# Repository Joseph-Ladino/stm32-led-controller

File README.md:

# STM32 WS2815 LED Controller

This is a hobby project using an STM32 microcontroller to control WS2815 LED strips over ethernet. While it’s a ~fun~ interesting setup, it’s still a work in progress, so the design and code have plenty of room for improvement.

## Hardware Overview

The controller is built around a custom PCB and features:

- **Microcontroller**: STM32G0B0RE, which handles LED effects, strip control, and MQTT connection.
- **Ethernet**: W5500 chip (from Wiznet) for simple 100/10 ethernet functionality.
- **LED Connection**: 4-pin connector for attaching WS2815 LED strips.
- **Debugging Options**:
  - **SWD (Serial Wire Debug)**: Required for flashing firmware.
  - **USB-C Port**: Used mainly for serial output, with optional 5V power.
- **Power Setup**:
  - **12V Power Connector**: Powers the LED strip, switched on/off with a software-controlled load switch. The power connector is subject to change in a future board REV but for now the power leads are attached using M4 machine screws.
  - **Buck Converter**: Steps down 12V to 5V for the data signals to the LEDs and to power the STM32 and ethernet chip.

*Known Issues*: 
  - The pads' hole size for the 4-pin LED strip connector is too small to easily fit the wires.

## Firmware Details

The firmware is written in C++ with portability and extensibility as guiding principles:

- **Connectivity**: Includes partially complete, platform-independent abstractions for network interface, sockets, and MQTT client, allowing connection to MQTT servers. Implementations relies on open-source libraries but the design allows these libraries to be swapped out relatively easily.
- **LED Strip Compatibility**: The firmware’s design allows control beyond the WS2815, with flexibility for WS2812, WS2811, and potentially other types through a semi-extensible interface. Currently, communication is handled by DMA timers and a circular buffer, but this setup supports future implementations.
- **Configurable, Extensible Architecture**: Aiming for maximum configurability, the design focuses on semi-modular components that can be swapped or extended easily.
- **Documentation**: Classes are documented using Doxygen. You can find a compiled HTML version in the `Firmware/Docs` folder.

*Known Issues*: 
  - The MQTT connection intermittently drops despite active ethernet indicators (likely a bug in the reconnect code).

---

## Getting Started

To try it out:

1. **Connect Power and LEDs**:
   - Screw down a 12V power source onto the marked.
   - Attach a WS2815 LED strip to the 4-pin connector.
   
2. **Upload Firmware**:
   - Firmware currently needs to be flashed over the SWD connector.

3. **Run and Debug**:
   - Connect the USB-C port for serial output or use SWD for debugging.

## Specs

| Feature                   | Description                                       |
|---------------------------|---------------------------------------------------|
| Microcontroller           | STM32G0B0RE                                       |
| Ethernet                  | W5500 (100/10 Ethernet)                           |
| LED Output Connector      | 4-pin (for WS2815 LED strip)                      |
| Debugging                 | USB-C, SWD for flashing      |
| Power Input               | 12V screw terminal                                |
| Voltage Conversion        | Buck converter (12V to 5V)                        |
| Data Buffer               | SN74125N for 5V data signals                      |
| Regulator                 | 3.3V for STM32 and W5500                          |

---

### Notes

This project is more of a learning exercise in PCB design and STM32 programming, so it might not be the most optimized controller out there! Any feedback or suggestions are welcome.

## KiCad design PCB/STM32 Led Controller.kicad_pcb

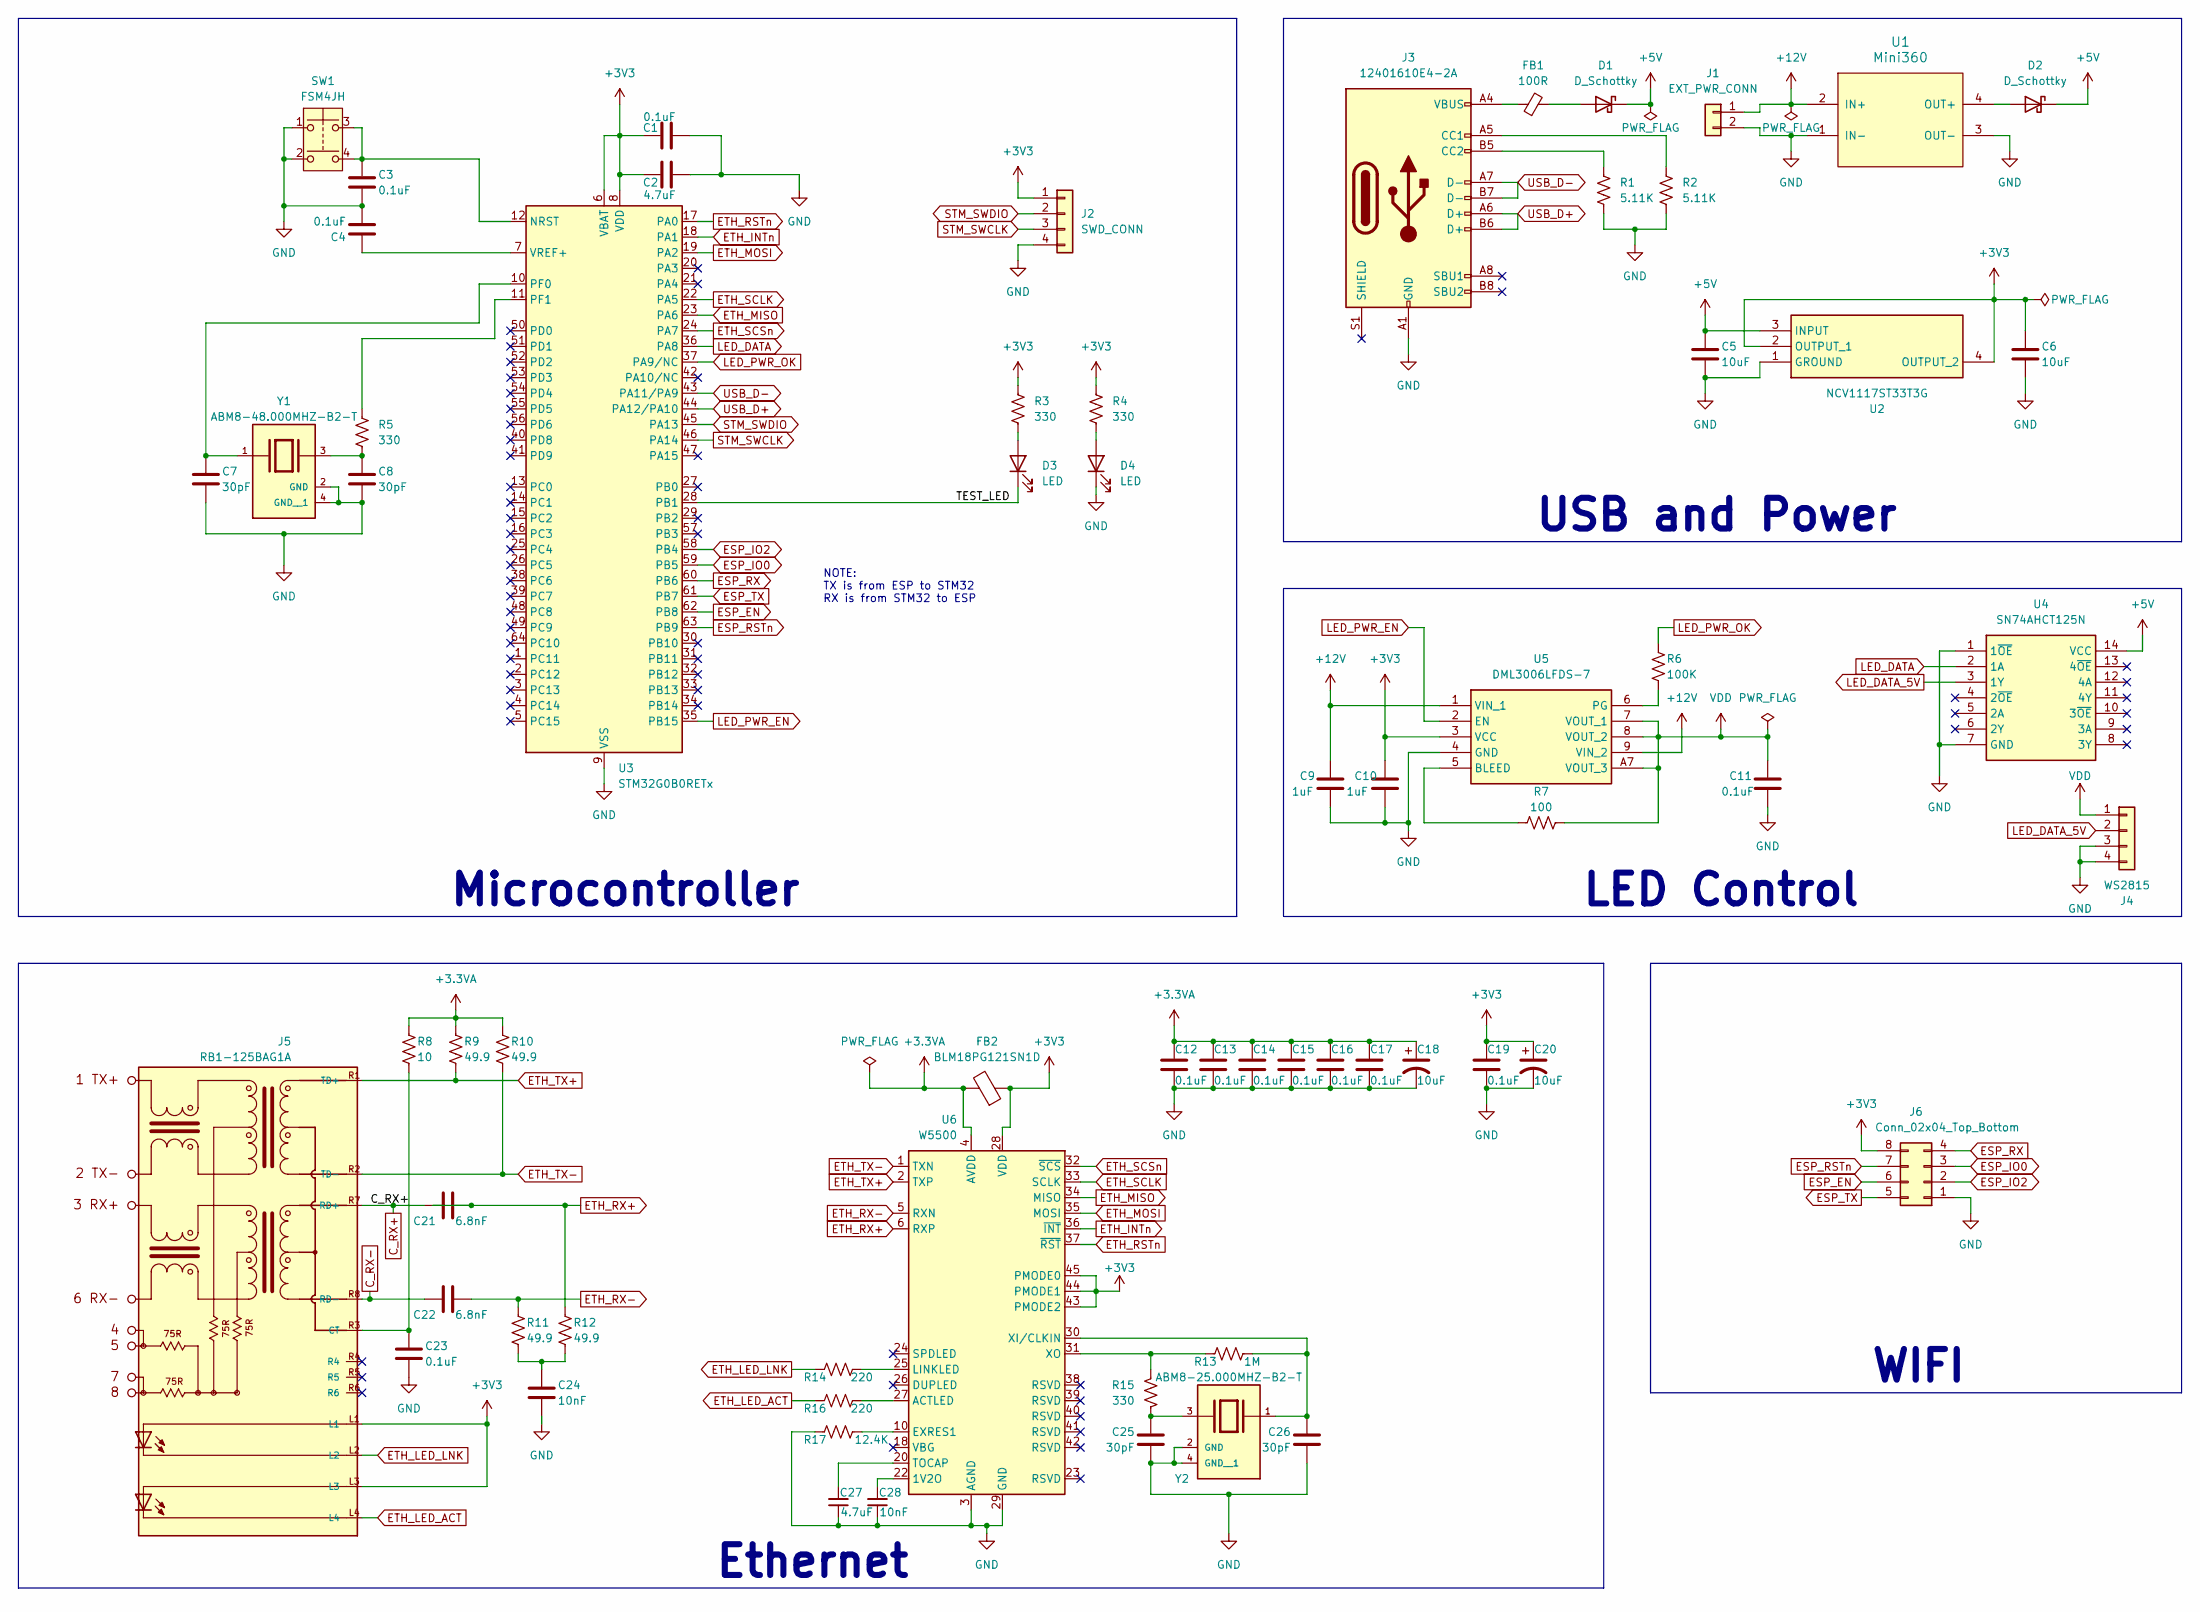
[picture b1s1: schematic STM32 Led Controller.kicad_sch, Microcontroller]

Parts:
C1, C3, C4, C11, C12, C13, C14, C15, C16, C17, C19, C23: 0.1uF; C_0603_1608Metric
C2, C27: 4.7uF; C_0603_1608Metric
C5, C6: 10uF; C_0805_2012Metric
C7, C8, C25, C26: 30pF; C_0603_1608Metric
C9, C10: 1uF; C_0603_1608Metric
C18, C20: 10uF; CP_Elec_4x5.3
C21, C22: 6.8nF; C_0603_1608Metric
C24, C28: 10nF; C_0603_1608Metric
D1, D2: D_Schottky; D_SMA-SMB_Universal_Handsoldering
D3, D4: LED; LED_0603_1608Metric
FB1: 100R; L_0805_2012Metric
FB2: BLM18PG121SN1D; BLM18SP221SN1B; Manufacturer_Part_Number BLM18PG121SN1D; Mouser Part Number 81-BLM18PG121SN1D
J1: EXT_PWR_CONN; 1x02 M4 RING
J2: SWD_CONN; PinHeader_1x04_P2.54mm_Vertical
J3: 12401610E4-2A; USB_C_Receptacle_Amphenol_12401610E4-2A
J4: WS2815; LED Strip Connector
J5: RB1-125BAG1A; WIZNET_RB1-125BAG1A
J6: Conn_02x04_Top_Bottom; PinSocket_2x04_P2.54mm_Vertical
R1, R2: 5.11K; R_0603_1608Metric
R3, R4, R5, R15: 330; R_0603_1608Metric
R6: 100K; R_0603_1608Metric
R7: 100; R_0603_1608Metric
R8: 10; R_0603_1608Metric
R9, R10, R11, R12: 49.9; R_0603_1608Metric
R13: 1M; R_0603_1608Metric
R14, R16: 220; R_0603_1608Metric
R17: 12.4K; R_0603_1608Metric
SW1: FSM4JH; Manufacturer_Part_Number FSM4JH; Mouser Part Number 506-FSM4JH
U1: Mini360; Mini360_step-down
U2: NCV1117ST33T3G; SOT230P700X180-4N; Manufacturer_Part_Number NCV1117ST33T3G; Mouser Part Number 863-NCV1117ST33T3G
U3: STM32G0B0RETx; LQFP-64_10x10mm_P0.5mm
U4: SN74AHCT125N; DIP794W53P254L1930H508Q14N; Manufacturer_Part_Number SN74AHCT125N; Mouser Part Number 595-SN74AHCT125N
U5: DML3006LFDS-7; DML3006LFDS7; Mouser Part Number 621-DML3006LFDS-7
U6: W5500; LQFP-48_7x7mm_P0.5mm
Y1: ABM8-48.000MHZ-B2-T; XTAL_ABM8-48.000MHZ-B2-T; PARTREV 44041
Y2: ABM8-25.000MHZ-B2-T; XTAL_ABM8-48.000MHZ-B2-T; PARTREV 44041

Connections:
+3.3VA: C12.1, C13.1, C14.1, C15.1, C16.1, C17.1, C18.1, FB2.2, R8.1, R9.1, R10.1, U6.4 (AVDD), U6.8 (AVDD), U6.11 (AVDD), U6.15 (AVDD), U6.17 (AVDD), U6.21 (AVDD)
+3V3: C1.1, C2.1, C6.1, C10.2, C19.1, C20.1, FB2.1, J2.1, J5.L1, J5.L3, J6.8, R3.1, R4.1, U2.2 (OUTPUT_1), U2.4 (OUTPUT_2), U3.6 (VBAT), U3.8 (VDD), U5.3 (VCC), U6.28 (VDD), U6.43 (PMODE2), U6.44 (PMODE1), U6.45 (PMODE0)
+5V: C5.1, D1.1 (K), D2.1 (K), U2.3 (INPUT), U4.14 (VCC)
+12V: C9.2, J1.1, U1.2 (IN+), U5.1 (VIN_1), U5.9 (VIN_2)
/TEST_LED: D3.1 (K), U3.28 (PB1)
C_RX+: C21.1, J5.R7 (RD+)
C_RX-: C22.1, J5.R8 (RD-)
ESP_EN: J6.6, U3.62 (PB8)
ESP_IO0: J6.3, U3.59 (PB5)
ESP_IO2: J6.2, U3.58 (PB4)
ESP_RSTn: J6.7, U3.63 (PB9)
ESP_RX: J6.4, U3.60 (PB6)
ESP_TX: J6.5, U3.61 (PB7)
ETH_INTn: U3.18 (PA1), U6.36 (~INT)
ETH_LED_ACT: J5.L4, R16.2
ETH_LED_LNK: J5.L2, R14.2
ETH_MISO: U3.23 (PA6), U6.34 (MISO)
ETH_MOSI: U3.19 (PA2), U6.35 (MOSI)
ETH_RSTn: U3.17 (PA0), U6.37 (~RST)
ETH_RX+: C21.2, R12.1, U6.6 (RXP)
ETH_RX-: C22.2, R11.1, U6.5 (RXN)
ETH_SCLK: U3.22 (PA5), U6.33 (SCLK)
ETH_SCSn: U3.24 (PA7), U6.32 (~SCS)
ETH_TX+: J5.R1 (TD+), R9.2, U6.2 (TXP)
ETH_TX-: J5.R2 (TD-), R10.2, U6.1 (TXN)
GND: C1.2, C2.2, C3.2, C4.2, C5.2, C6.2, C7.2, C8.2, C9.1, C10.1, C11.1, C12.2, C13.2, C14.2, C15.2, C16.2, C17.2, C18.2, C19.2, C20.2, C23.2, C24.2, C25.2, C26.2, C27.1, C28.1, D4.1 (K), J1.2, J2.4, J3.A1 (GND), J3.A12 (GND), J3.B1 (GND), J3.B12 (GND), J4.3, J4.4, J6.1, R1.2, R2.2, R17.2, SW1.1, SW1.2, U1.1 (IN-), U1.3 (OUT-), U2.1 (GROUND), U3.9 (VSS), U4.1 (1~OE), U4.7 (GND), U5.4 (GND), U6.3 (AGND), U6.9 (AGND), U6.14 (AGND), U6.16 (AGND), U6.19 (AGND), U6.29 (GND), U6.48 (AGND), Y1.2 (GND), Y1.4 (GND__1), Y2.2 (GND), Y2.4 (GND__1)
LED_DATA: U3.36 (PA8), U4.2 (1A)
LED_DATA_5V: J4.2, U4.3 (1Y)
LED_PWR_EN: U3.35 (PB15), U5.2 (EN)
LED_PWR_OK: R6.2, U3.37 (PA9/NC)
unnamed: C8.1, R5.1, Y1.3
unnamed: C24.1, R11.2, R12.2
unnamed: C25.1, R15.1, Y2.3
unnamed: D1.2 (A), FB1.2
unnamed: D2.2 (A), U1.4 (OUT+)
unnamed: D3.2 (A), R3.2
unnamed: D4.2 (A), R4.2
unnamed: FB1.1, J3.A4 (VBUS), J3.A9 (VBUS), J3.B4 (VBUS), J3.B9 (VBUS)
unnamed: J3.A5 (CC1), R2.1
unnamed: J3.B5 (CC2), R1.1
unnamed: C23.1, J5.R3 (CT), R8.2
unnamed: C3.1, SW1.3, SW1.4, U3.12 (NRST)
unnamed: C7.1, U3.10 (PF0), Y1.1
unnamed: R5.2, U3.11 (PF1)
unnamed: C4.1, U3.7 (VREF+)
unnamed: R7.1, U5.5 (BLEED)
unnamed: R6.1, U5.6 (PG)
unnamed: C28.2, U6.22 (1V2O)
unnamed: R16.1, U6.27 (ACTLED)
unnamed: R17.1, U6.10 (EXRES1)
unnamed: R14.1, U6.25 (LINKLED)
unnamed: C27.2, U6.20 (TOCAP)
unnamed: C26.1, R13.1, U6.30 (XI/CLKIN), Y2.1
unnamed: R13.2, R15.2, U6.31 (XO)
STM_SWCLK: J2.3, U3.46 (PA14)
STM_SWDIO: J2.2, U3.45 (PA13)
USB_D+: J3.A6 (D+), J3.B6 (D+), U3.44 (PA12/PA10)
USB_D-: J3.A7 (D-), J3.B7 (D-), U3.43 (PA11/PA9)
VDD: C11.2, J4.1, R7.2, U5.7 (VOUT_1), U5.8 (VOUT_2), U5.A7 (VOUT_3)

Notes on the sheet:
USB and Power
LED Control
WIFI
Ethernet
Microcontroller
NOTE: TX is from ESP to STM32 RX is from STM32 to ESP

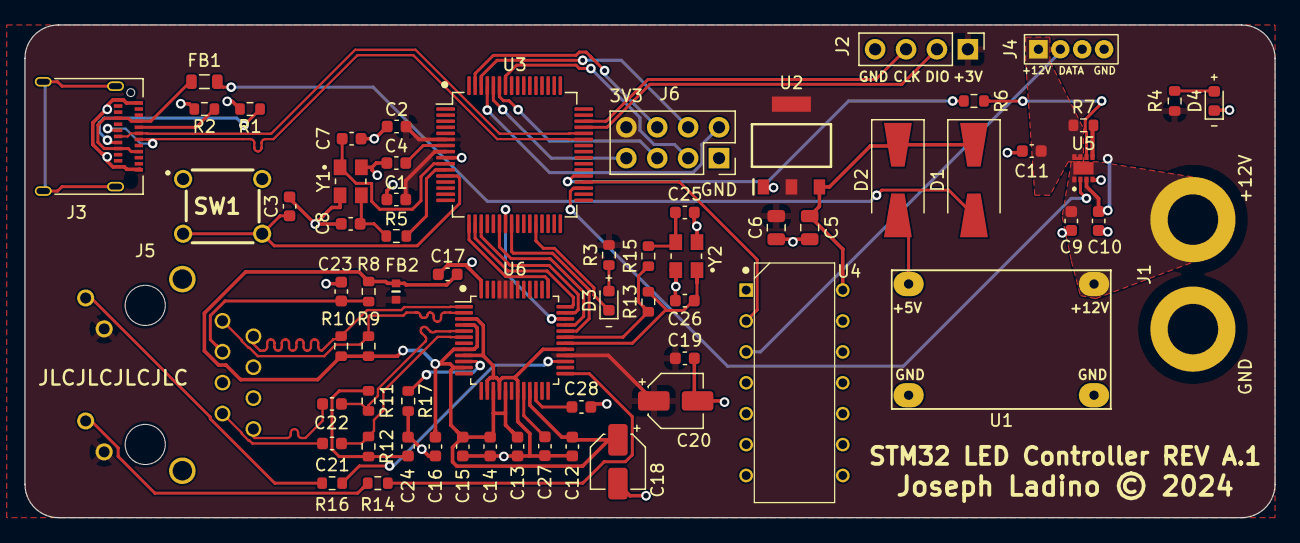
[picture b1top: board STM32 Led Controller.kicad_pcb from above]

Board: 2 copper layers, 102.8 x 40.5 mm, 67 parts (1 on the bottom side), 59 nets.

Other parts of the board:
svg2mod: G***; logo

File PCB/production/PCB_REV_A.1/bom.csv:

Designator,Footprint,Quantity,Value,LCSC Part #
"C1, C11, C12, C13, C14, C15, C16, C17, C19, C23, C3, C4",0603,12,0.1uF,
"C10, C9",0603,2,1uF,
"C18, C20",CP_Elec_4x5.3,2,10uF,
"C2, C27",0603,2,4.7uF,
"C21, C22",0603,2,6.8nF,
"C24, C28",0603,2,10nF,
"C25, C26, C7, C8",0603,4,30pF,
"C5, C6",0805,2,10uF,
"D1, D2",D_SMA-SMB_Universal_Handsoldering,2,D_Schottky,
"D3, D4",0603,2,LED,
FB1,0805,1,100R,
FB2,BLM18SP221SN1B,1,BLM18PG121SN1D,
J1,1x02 M4 RING,1,EXT_PWR_CONN,
J2,PinHeader_1x04_P2.54mm_Vertical,1,SWD_CONN,
J3,USB_C_Receptacle_Amphenol_12401610E4-2A,1,12401610E4-2A,
J4,LED Strip Connector,1,WS2815,
J5,WIZNET_RB1-125BAG1A,1,RB1-125BAG1A,
J6,PinSocket_2x04_P2.54mm_Vertical,1,Conn_02x04_Top_Bottom,
"R1, R2",0603,2,5.11K,
"R10, R11, R12, R9",0603,4,49.9,
R13,0603,1,1M,
"R14, R16",0603,2,220,
"R15, R3, R4, R5",0603,4,330,
R17,0603,1,12.4K,
R6,0603,1,100K,
R7,0603,1,100,
R8,0603,1,10,
SW1,FSM4JH,1,FSM4JH,
U1,Mini360_step-down,1,Mini360,
U2,SOT230P700X180-4N,1,NCV1117ST33T3G,
U3,LQFP-64_10x10mm_P0.5mm,1,STM32G0B0RETx,
U4,DIP794W53P254L1930H508Q14N,1,SN74AHCT125N,
U5,DML3006LFDS7,1,DML3006LFDS-7,
U6,LQFP-48_7x7mm_P0.5mm,1,W5500,
Y1,XTAL_ABM8-48.000MHZ-B2-T,1,ABM8-48.000MHZ-B2-T,
Y2,XTAL_ABM8-48.000MHZ-B2-T,1,ABM8-25.000MHZ-B2-T,

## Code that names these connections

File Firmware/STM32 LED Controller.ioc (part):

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Mcu.Name=STM32G0B0RETx
Mcu.Package=LQFP64
Mcu.UserName=STM32G0B0RETx
PA0.GPIOParameters=PinState,GPIO_PuPd,GPIO_Label,GPIO_ModeDefaultOutputPP
PA0.GPIO_Label=ETH_RSTn
PA0.GPIO_ModeDefaultOutputPP=GPIO_MODE_OUTPUT_PP
PA0.GPIO_PuPd=GPIO_NOPULL
PA0.PinState=GPIO_PIN_SET
PA0.Signal=GPIO_Output
PA1.GPIOParameters=GPIO_Label
PA1.GPIO_Label=ETH_INTn
PA1.Signal=GPXTI1
PA11\ [PA9].Mode=Device
PA11\ [PA9].Signal=USB_DM
PA12\ [PA10].Mode=Device
PA12\ [PA10].Signal=USB_DP
PA13.Mode=Serial_Wire
PA13.Signal=SYS_SWDIO
PA14-BOOT0.Mode=Serial_Wire
PA14-BOOT0.Signal=SYS_SWCLK
PA2.Mode=Full_Duplex_Master
PA2.Signal=SPI1_MOSI
PA5.Mode=Full_Duplex_Master
PA5.Signal=SPI1_SCK
PA6.Mode=Full_Duplex_Master
PA6.Signal=SPI1_MISO
PA7.GPIOParameters=PinState,GPIO_Label
PA7.GPIO_Label=ETH_SCSn
PA7.PinState=GPIO_PIN_SET
PA7.Signal=GPIO_Output
PA8.GPIOParameters=GPIO_Speed,GPIO_Label
PA8.GPIO_Label=LED_DATA
PA8.GPIO_Speed=GPIO_SPEED_FREQ_VERY_HIGH
PA8.Signal=S_TIM1_CH1
PA9.GPIOParameters=GPIO_PuPd,GPIO_Label
PA9.GPIO_Label=LED_PWR_OK
PA9.GPIO_PuPd=GPIO_PULLUP
PA9.Signal=GPIO_Input
PB1.GPIOParameters=GPIO_PuPd,GPIO_Label,GPIO_ModeDefaultOutputPP
PB1.GPIO_Label=TEST_LED
PB1.GPIO_ModeDefaultOutputPP=GPIO_MODE_OUTPUT_PP
PB1.GPIO_PuPd=GPIO_NOPULL
PB1.Signal=GPIO_Output
PB15.GPIOParameters=GPIO_Label
PB15.GPIO_Label=LED_PWR_EN
PB15.Signal=GPIO_Output
PB4.GPIOParameters=GPIO_Label
PB4.GPIO_Label=ESP_IO2
PB4.Signal=GPIO_Output
PB5.GPIOParameters=GPIO_Label
PB5.GPIO_Label=ESP_IO0
PB5.Signal=GPIO_Output
PB6.Mode=Asynchronous
PB6.Signal=USART1_TX
PB7.Mode=Asynchronous
PB7.Signal=USART1_RX
PB8.GPIOParameters=GPIO_Label
PB8.GPIO_Label=ESP_EN
PB8.Signal=GPIO_Output
PB9.GPIOParameters=GPIO_Label
PB9.GPIO_Label=ESP_RSTn
PB9.Signal=GPIO_Output
PF0-OSC_IN\ (PF0).Mode=HSE-External-Oscillator
PF0-OSC_IN\ (PF0).Signal=RCC_OSC_IN
PF1-OSC_OUT\ (PF1).Mode=HSE-External-Oscillator
PF1-OSC_OUT\ (PF1).Signal=RCC_OSC_OUT
RCC.HSE_VALUE=48000000
RCC.SYSCLKFreq_VALUE=64000000
RCC.SYSCLKSource=RCC_SYSCLKSOURCE_PLLCLK
board=custom

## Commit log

2024-01-12 Moving schematic to Kicad from Altium (because Altium sucks)
    Added most of 'Microcontroller' section
    Added 'USB and power' section
    Began 'LED Controller' section
2024-01-16 Tweaked schematic Initial PCB layout/wiring (subject to change) Still need to add name/rev to silk screen
2024-01-16 restructured project folder
2024-01-16 repository stuff
2024-01-21 Moved connectors Finished routing Add filleted corners Added name to silkmask Ordered board, REV A complete
2024-02-05 minor tweaks, added logo, adjusted silkscreen
2024-02-05 began firmware development
2024-02-07 tweaked PCB, updated firmware
2024-02-07 added driver for W5500. NOTE: not yet configured or building in STM32CubeIDE
2024-02-08 Configured STM32CubeIDE to use include and build ioLibrary
2024-02-08 cleaned up build files, added gitignore
2024-02-10 Corrected DRC issues, generated build
2024-02-19 current firmware unable to connect through DHCP, WIP
2024-02-19 code now uses printf, lowered USB interrupt priority
2024-02-21 DHCP is now functional
    Able to receive IP information from router.
    Enabled timer 3 for 1 second interval interrupt. (needed for DHCP timeout);
    Codebase needs a refactor before continuing
2024-02-22 started rewrite
2024-02-23 Added higher level EthernetHC interface
2024-02-26 Refactored Ethernet Interface
    Tweaked EthernetHC interface
    Implemented W5500HC class
    restructured and debloated W5500Interface class
    W5500Interface will likely be renamed in a future commit
2024-03-06 Added PAHO-MQTT library
    added mqtt library as submodule because the version bundled with wiznet ioLibrary is out of date. To future me: use library by including/cloning interface from ioLibrary/mqttt_interface
2024-03-10 began working on MQTT
    currently using ioLibrary's mqtt_interface files to get things working. Refactor likely will be needed in the future
2024-03-16 Lots of Refactor + Breaking Changes
    MQTT now "works"
    Restructured project files (interfaces in JLIB, implementation (mainly) in Core/JPort)
    In progress refactor of networking/socket code to use more generic classes
    In progress wrapper class for MQTTClient (incase I change MQTT libraries in the future)
    Potentially adding unit testing in the future
2024-03-17 Configured googletest + work on socket wrapper
    Googletest configured to build using MSYS2 mingw64 installed on system path
    Some basic tests written (more for practice than anything)
    Modified hardware controller to return available socket
    Integrating JLib classes (CountdownTimer, W5500Socket, etc) into pre-existing classes for a more consistent feel
2024-03-18 MQTTClient wrapper + size optimizations
    general refactors to codebase with breaking changes of course
    began creating a mqtt client wrapper (currently only supports connecting to a socket and publishing messages)
    began replacing some cstrings with std::string_view
    enabled debug optimization in compiler settings (compiled code size has shrunk 20kb)
2024-03-18 update mqtt submodule fork
    did a thing
2024-03-21 updated mqtt client functionality, using std::string instead of std::string_view
2024-03-21 moved connect() to private
2024-03-24 updated reconnect code began working on Color class
2024-04-26 Began adding Doxygen documentation
    Renamed networking classes
    DOCS generated for NetConfig, NetIP, NetMAC, and NetSock
2024-04-26 Merge Stashed Changes
    BUILD_WITHOUT_SECRETS defined to allow testing without connecting socket to server
2024-07-09 Implemented DMA and tweaks to socket code
2024-07-10 Major Updates to MQTT system
    Client now registers multiple message receivers using observer pattern
    Client differentiates between a generic message receiver and a specific message receiver (receives only messages from a specified topic)
    HomeAssistantStrip class will have control over LEDs, DMA, and MQTT
    Fixed bug with paho-embedded-client calling JMQTT::PAHOClient message handlers repeatedly
2024-07-13 Implemented MQTT connection to Homeassistant
    Strip connects to homeassistant
    Moved brightness scaling into WS2815Strip
    Fixed bugs in DMAStrip
    Cleaned up some build warnings
    QOL improvements to various classes
2024-07-14 Began ledstrip refactor & updated formatting rules
    buffers for ledstrip and dmastrip classes will now be externally allocated
    support for rgbw and different color orderings added
    lines now allowed to be 120 char long
2024-07-14 more formatting
2024-07-15 Strip Refactor mostly complete
    classes will be tweaked in upcoming commits
    MQTT will control will not be implemented by inheriting from DMAStrip like previously done
2024-07-17 Rewrite of LEDStrip driver almost complete
    Added gamma/color/temperature correction
    Changed WS28xxStrip inheritance.
    Updated WSStrpState
    Added MQTT support for new strip (subject to modification)
    Added StringBuilder class (may be deleted soon)
2024-07-27 Release Build Bug Fix
    Bug in logic in PAHOClient caused release builds to not dispatch client messages. Corrected guard clause conditions in pahoMessageReceived() to fix
2026-03-27 DOCS + Libs + Attempt to squash reconnect bugs
2026-03-27 hello jlib?
2026-03-27 convert JLib from separate repo to normal folder

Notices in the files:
PCB/STM32 Led Controller.kicad_pcb:
Joseph Ladino️ © 2024
